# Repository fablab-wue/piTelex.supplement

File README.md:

# - piTelex.supplement

This project hold the additional files for the teletype project [piTelex](https://github.com/fablab-wue/piTelex)

**[For more informations see the WIKI pages](https://github.com/fablab-wue/piTelex/wiki)**

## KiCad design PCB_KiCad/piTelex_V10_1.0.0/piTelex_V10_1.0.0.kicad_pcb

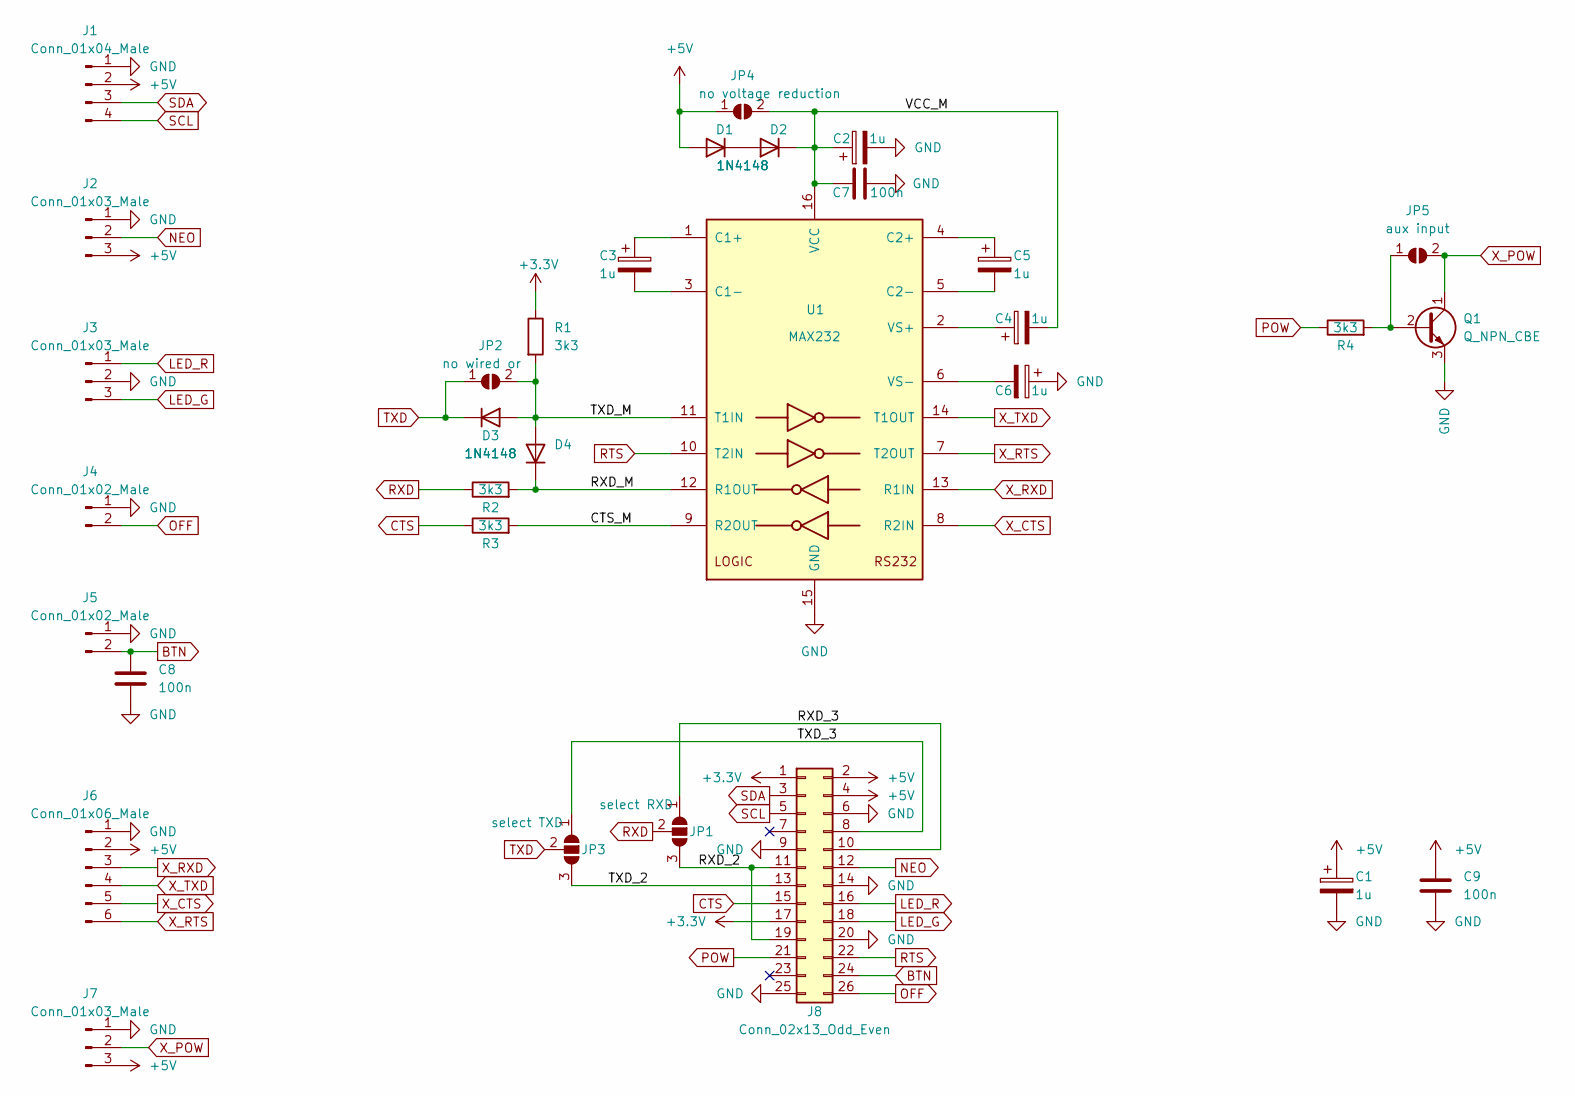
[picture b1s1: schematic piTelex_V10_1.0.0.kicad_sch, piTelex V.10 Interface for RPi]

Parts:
C1, C2, C3, C4, C5, C6: 1u; CP_Radial_D4.0mm_P2.00mm
C7, C8, C9: 100n; C_Disc_D3.4mm_W2.1mm_P2.50mm
D1, D2, D3, D4: 1N4148; D_DO-35_SOD27_P7.62mm_Horizontal
J1: Conn_01x04_Male; PinHeader_1x04_P2.54mm_Vertical
J2, J3, J7: Conn_01x03_Male; PinHeader_1x03_P2.54mm_Vertical
J4, J5: Conn_01x02_Male; PinHeader_1x02_P2.54mm_Vertical
J6: Conn_01x06_Male; PinHeader_1x06_P2.54mm_Vertical
J8: Conn_02x13_Odd_Even; PinSocket_2x13_P2.54mm_Vertical
JP1: select RXD; SolderJumper-3_P1.3mm_Open_Pad1.0x1.5mm
JP2: no wired or; SolderJumper-2_P1.3mm_Open_Pad1.0x1.5mm
JP3: select TXD; SolderJumper-3_P1.3mm_Open_Pad1.0x1.5mm
JP4: no voltage reduction; SolderJumper-2_P1.3mm_Open_Pad1.0x1.5mm
JP5: aux input; SolderJumper-2_P1.3mm_Open_Pad1.0x1.5mm
Q1: Q_NPN_CBE; TO-92L
R1, R2, R3, R4: 3k3; R_Axial_DIN0207_L6.3mm_D2.5mm_P10.16mm_Horizontal
U1: MAX232; DIP-16_W7.62mm

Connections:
+3.3V: J8.1, J8.17, R1.1
+5V: C1.1, C9.1, D1.2 (A), J1.2, J2.3, J6.2, J7.3, J8.2, J8.4, JP4.1 (A)
/CTS_M: R3.2, U1.9 (R2OUT)
/RXD_2: J8.11, J8.19, JP1.3 (B)
/RXD_3: J8.10, JP1.1 (A)
/RXD_M: D4.1 (K), R2.2, U1.12 (R1OUT)
/TXD_2: J8.13, JP3.3 (B)
/TXD_3: J8.8, JP3.1 (A)
/TXD_M: D3.2 (A), D4.2 (A), JP2.2 (B), R1.2, U1.11 (T1IN)
/VCC_M: C2.1, C4.2, C7.1, D2.1 (K), JP4.2 (B), U1.16 (VCC)
BTN: C8.1, J5.2, J8.24
CTS: J8.15, R3.1
GND: C1.2, C2.2, C6.1, C7.2, C8.2, C9.2, J1.1, J2.1, J3.2, J4.1, J5.1, J6.1, J7.1, J8.6, J8.9, J8.14, J8.20, J8.25, Q1.3 (E), U1.15 (GND)
LED_G: J3.3, J8.18
LED_R: J3.1, J8.16
NEO: J2.2, J8.12
unnamed: C3.1, U1.1 (C1+)
unnamed: C3.2, U1.3 (C1-)
unnamed: C4.1, U1.2 (VS+)
unnamed: C5.1, U1.4 (C2+)
unnamed: C5.2, U1.5 (C2-)
unnamed: C6.2, U1.6 (VS-)
unnamed: D1.1 (K), D2.2 (A)
unnamed: JP5.1 (A), Q1.2 (B), R4.2
OFF: J4.2, J8.26
POW: J8.21, R4.1
RTS: J8.22, U1.10 (T2IN)
RXD: JP1.2 (C), R2.1
SCL: J1.4, J8.5
SDA: J1.3, J8.3
TXD: D3.1 (K), JP2.1 (A), JP3.2 (C)
X_CTS: J6.5, U1.8 (R2IN)
X_POW: J7.2, JP5.2 (B), Q1.1 (C)
X_RTS: J6.6, U1.7 (T2OUT)
X_RXD: J6.3, U1.13 (R1IN)
X_TXD: J6.4, U1.14 (T1OUT)

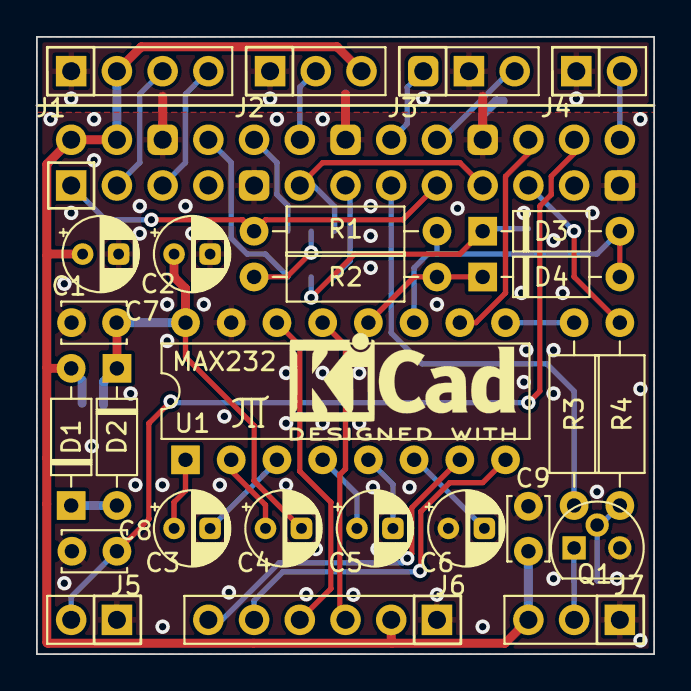
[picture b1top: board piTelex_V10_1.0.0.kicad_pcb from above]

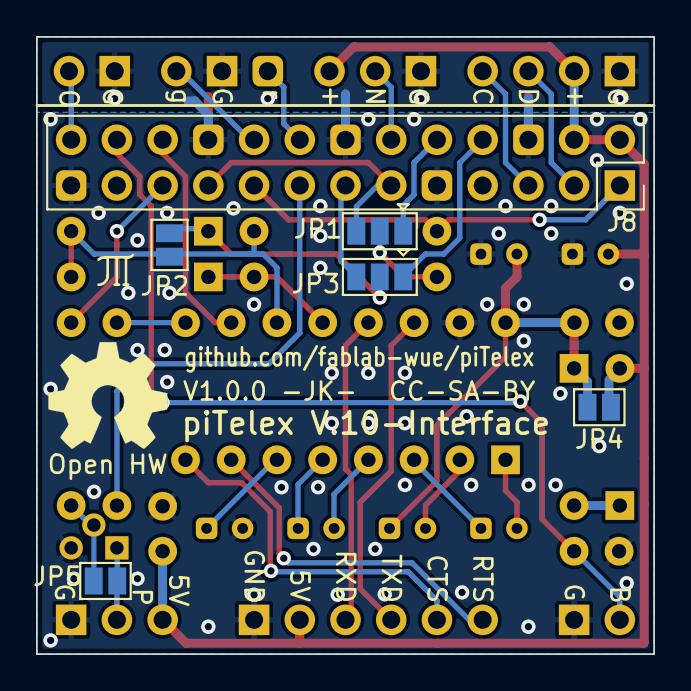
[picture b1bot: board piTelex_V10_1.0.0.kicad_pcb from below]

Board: 2 copper layers, 34.3 x 34.3 mm, 32 parts (6 on the bottom side), 36 nets.

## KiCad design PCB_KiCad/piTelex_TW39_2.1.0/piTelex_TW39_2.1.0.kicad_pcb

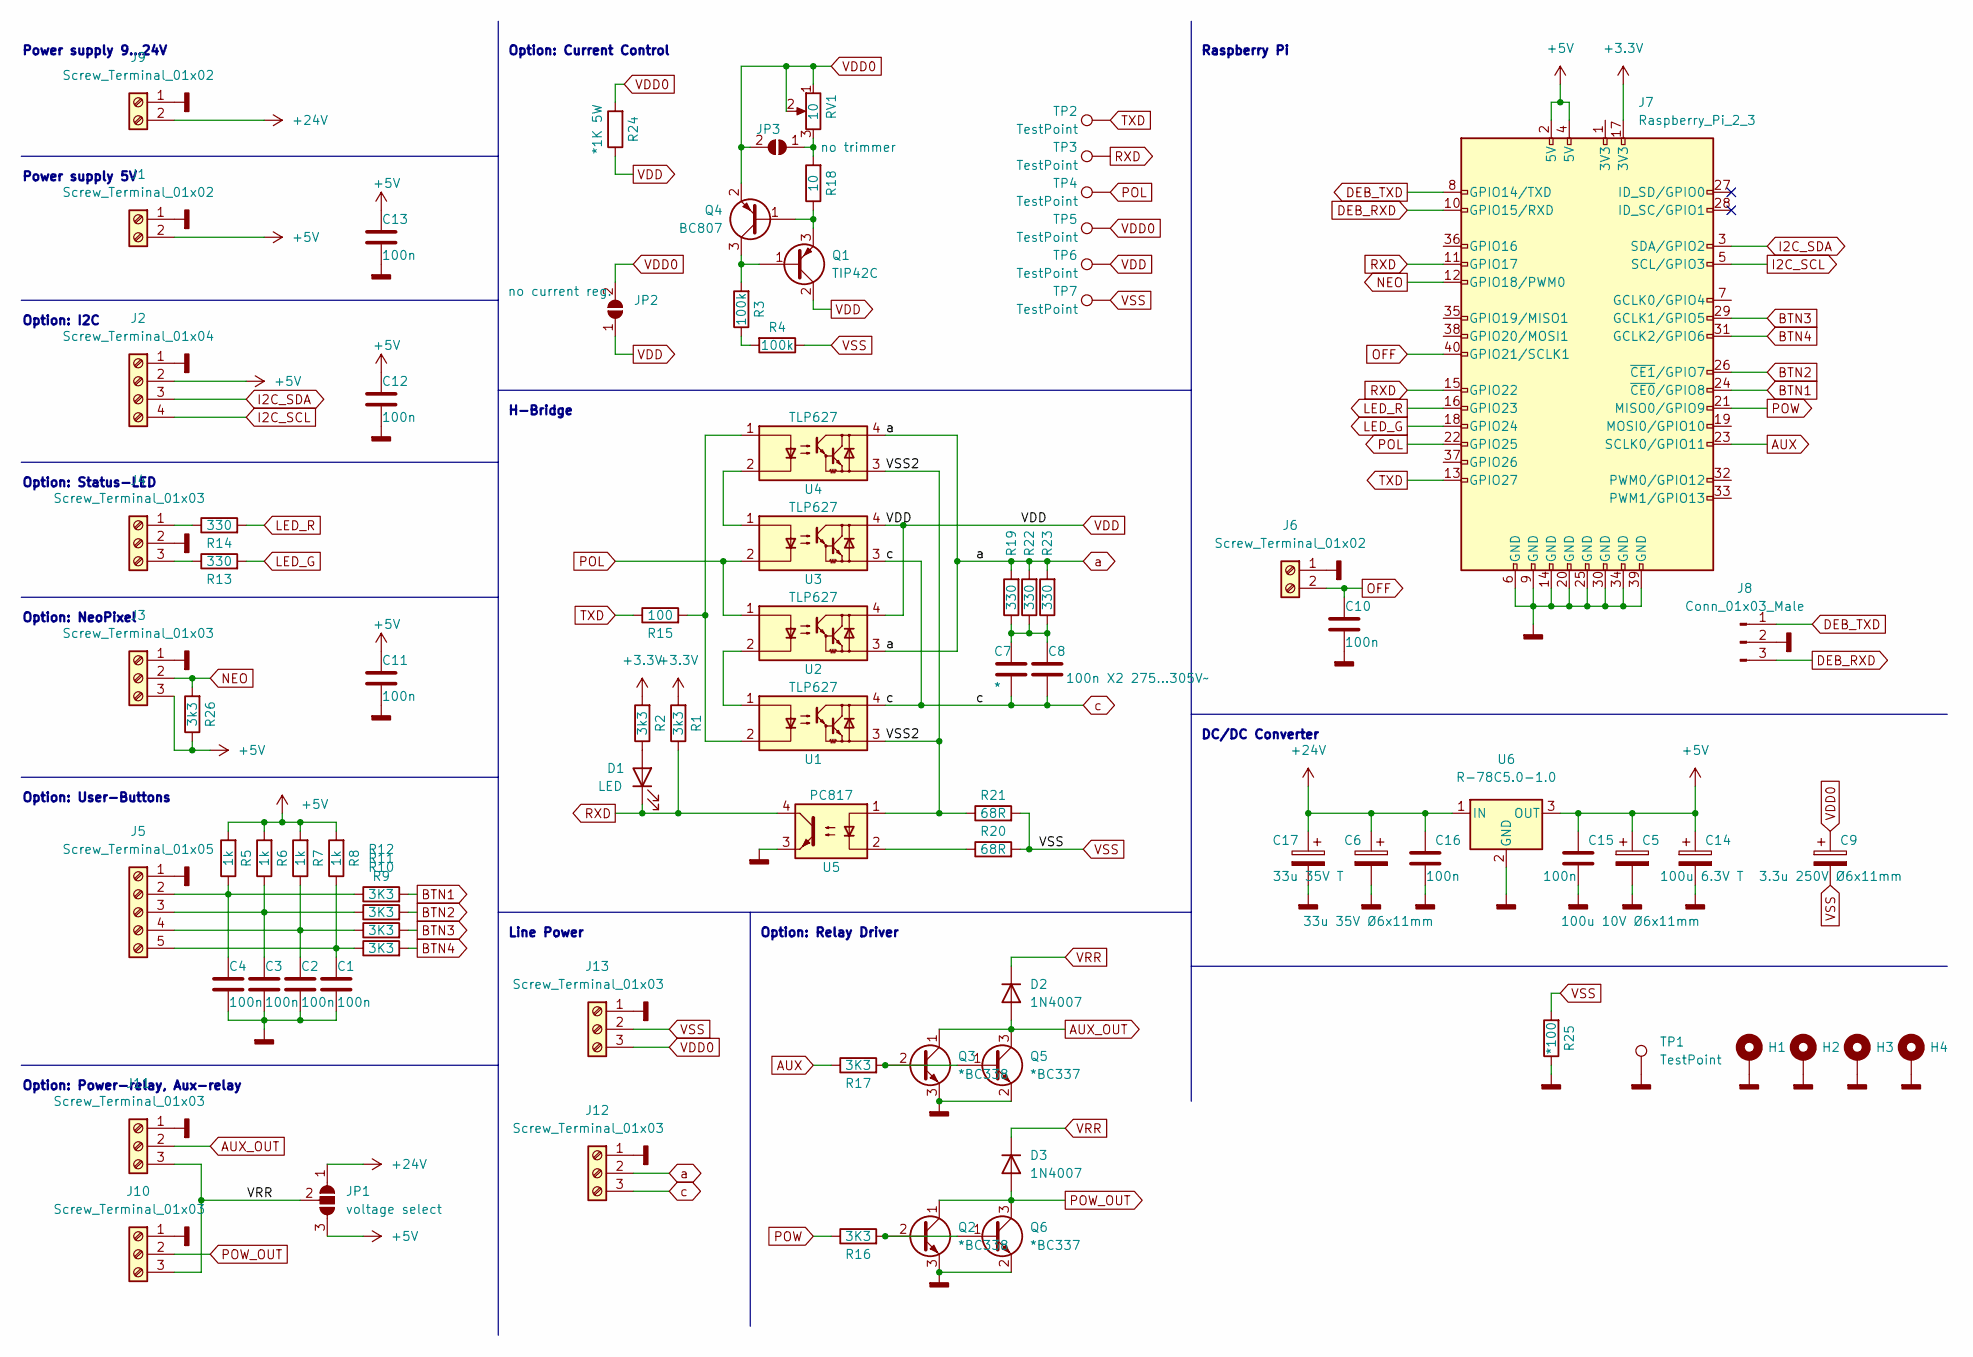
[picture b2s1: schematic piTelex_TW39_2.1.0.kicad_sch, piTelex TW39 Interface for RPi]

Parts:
C1, C2, C3, C4, C10, C11, C12, C13, C15, C16: 100n; C_0805_2012Metric_Pad1.18x1.45mm_HandSolder
C5: 100u 10V Ø6x11mm; CP_Radial_D7.5mm_P2.50mm
C6: 33u 35V Ø6x11mm; CP_Radial_D7.5mm_P2.50mm
C7: *; C_Rect_L9.0mm_W4.2mm_P7.50mm_MKT
C8: 100n X2 275...305V~; C_Rect_L16.5mm_W6.0mm_P15.00mm_MKT
C9: 3.3u 250V Ø6x11mm; CP_Radial_D7.5mm_P2.50mm
C14: 100u 6.3V T; CP_EIA-7343-31_Kemet-D_Pad2.25x2.55mm_HandSolder
C17: 33u 35V T; CP_EIA-7343-31_Kemet-D_Pad2.25x2.55mm_HandSolder
D1: LED; LED_D5.0mm
D2, D3: 1N4007; D_SMB
H1, H2, H3, H4: MountingHole_Pad; MountingHole_2.7mm_M2.5_ISO7380_Pad
J1, J6, J9: Screw_Terminal_01x02; Molex_KK-254_AE-6410-02A_1x02_P2.54mm_Vertical
J2: Screw_Terminal_01x04; Molex_KK-254_AE-6410-04A_1x04_P2.54mm_Vertical
J3, J4, J10, J11, J12, J13: Screw_Terminal_01x03; Molex_KK-254_AE-6410-03A_1x03_P2.54mm_Vertical
J5: Screw_Terminal_01x05; Molex_KK-254_AE-6410-05A_1x05_P2.54mm_Vertical
J7: Raspberry_Pi_2_3; PinSocket_2x20_P2.54mm_Vertical
J8: Conn_01x03_Male; PinHeader_1x03_P2.54mm_Vertical
JP1: voltage select; SolderJumper-3_P1.3mm_Open_Pad1.0x1.5mm
JP2: no current reg.; SolderJumper-2_P1.3mm_Open_Pad1.0x1.5mm
JP3: no trimmer; SolderJumper-2_P1.3mm_Open_Pad1.0x1.5mm
Q1: TIP42C; TO-220-3_Vertical
Q2, Q3: *BC338; TO-92
Q4: BC807; SOT-23
Q5, Q6: *BC337; SOT-23
R1, R2, R26: 3k3; R_0805_2012Metric_Pad1.20x1.40mm_HandSolder
R3, R4: 100k; R_0805_2012Metric_Pad1.20x1.40mm_HandSolder
R5, R6, R7, R8: 1k; R_0805_2012Metric_Pad1.20x1.40mm_HandSolder
R9, R10, R11, R12, R16, R17: 3K3; R_0805_2012Metric_Pad1.20x1.40mm_HandSolder
R13, R14, R19, R22, R23: 330; R_0805_2012Metric_Pad1.20x1.40mm_HandSolder
R15: 100; R_0805_2012Metric_Pad1.20x1.40mm_HandSolder
R18: 10; R_0805_2012Metric_Pad1.20x1.40mm_HandSolder
R20, R21: 68R; R_0805_2012Metric_Pad1.20x1.40mm_HandSolder
R24: *1K 5W; R_Axial_Power_L25.0mm_W9.0mm_P30.48mm
R25: *100; R_0805_2012Metric_Pad1.20x1.40mm_HandSolder
RV1: 10; Potentiometer_Bourns_3299Z_Horizontal
TP1: TestPoint; Pin_D1.0mm_L10.0mm
TP2, TP3, TP4, TP5, TP6, TP7: TestPoint; TestPoint_Pad_D1.5mm
U1, U2, U3, U4: TLP627; DIP-4_W7.62mm
U5: PC817; DIP-4_W7.62mm
U6: R-78C5.0-1.0; Converter_DCDC_RECOM_R-78E-0.5_THT

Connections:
+3.3V: J7.17 (3V3), R1.2, R2.2
+5V: C5.1, C11.1, C12.1, C13.1, C14.1, C15.1, J1.2, J2.2, J3.3, J7.2 (5V), J7.4 (5V), JP1.3 (B), R5.2, R6.2, R7.2, R8.2, R26.1, U6.3 (OUT)
+24V: C6.1, C16.1, C17.1, J9.2, JP1.1 (A), U6.1 (IN)
/VSS2: R21.1, U1.3, U4.3, U5.1
AUX: J7.23 (SCLK0/GPIO11), R17.1
AUX_OUT: D2.2 (A), J11.2, Q3.1 (C), Q5.3 (C)
BTN1: J7.24 (~CE0/GPIO8), R12.2
BTN2: J7.26 (~CE1/GPIO7), R11.2
BTN3: J7.29 (GCLK1/GPIO5), R10.2
BTN4: J7.31 (GCLK2/GPIO6), R9.2
DEB_RXD: J7.10 (GPIO15/RXD), J8.3
DEB_TXD: J7.8 (GPIO14/TXD), J8.1
GNDD: C1.2, C2.2, C3.2, C4.2, C5.2, C6.2, C10.2, C11.2, C12.2, C13.2, C14.2, C15.2, C16.2, C17.2, H1.1, H2.1, H3.1, H4.1, J1.1, J2.1, J3.1, J4.2, J5.1, J6.1, J7.6 (GND), J7.9 (GND), J7.14 (GND), J7.20 (GND), J7.25 (GND), J7.30 (GND), J7.34 (GND), J7.39 (GND), J8.2, J9.1, J10.1, J11.1, J12.1, J13.1, Q2.3 (E), Q3.3 (E), Q5.2 (E), Q6.2 (E), R25.1, TP1.1, U5.3, U6.2 (GND)
I2C_SCL: J2.4, J7.5 (SCL/GPIO3)
I2C_SDA: J2.3, J7.3 (SDA/GPIO2)
LED_G: J7.18 (GPIO24), R13.2
LED_R: J7.16 (GPIO23), R14.2
NEO: J3.2, J7.12 (GPIO18/PWM0), R26.2
unnamed: C1.1, J5.5, R8.1, R9.1
unnamed: C2.1, J5.4, R7.1, R10.1
unnamed: C3.1, J5.3, R6.1, R11.1
unnamed: C4.1, J5.2, R5.1, R12.1
unnamed: C7.1, C8.1, R19.1, R22.1, R23.1
unnamed: J4.1, R14.1
unnamed: J4.3, R13.1
unnamed: Q3.2 (B), Q5.1 (B), R17.2
unnamed: Q1.3 (E), Q4.1 (B), R18.1
unnamed: Q1.1 (B), Q4.3 (C), R3.2
unnamed: Q2.2 (B), Q6.1 (B), R16.2
unnamed: D1.2 (A), R2.1
unnamed: R3.1, R4.2
unnamed: JP3.1 (A), R18.2, RV1.3
unnamed: U1.1, U2.2
unnamed: R15.2, U1.2, U4.1
unnamed: U3.1, U4.2
unnamed: R20.1, U5.2
OFF: C10.1, J6.2, J7.40 (GPIO21/SCLK1)
POL: J7.22 (GPIO25), TP4.1, U2.1, U3.2
POW: J7.21 (MISO0/GPIO9), R16.1
POW_OUT: D3.2 (A), J10.2, Q2.1 (C), Q6.3 (C)
RXD: D1.1 (K), J7.11 (GPIO17), J7.15 (GPIO22), R1.1, TP3.1, U5.4
TXD: J7.13 (GPIO27), R15.1, TP2.1
VDD: JP2.1 (A), Q1.2 (C), R24.1, TP6.1, U2.4, U3.4
VDD0: C9.1, J13.3, JP2.2 (B), JP3.2 (B), Q4.2 (E), R24.2, RV1.1, RV1.2, TP5.1
VRR: D2.1 (K), D3.1 (K), J10.3, J11.3, JP1.2 (C)
VSS: C9.2, J13.2, R4.1, R20.2, R21.2, R25.2, TP7.1
a: J12.2, R19.2, R22.2, R23.2, U2.3, U4.4
c: C7.2, C8.2, J12.3, U1.4, U3.3

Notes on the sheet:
Line Power
Option: Relay Driver
Option: Status-LED
Option: User-Buttons
Option: I2C
Raspberry Pi
Power supply 9...24V
Option: Current Control
Option: NeoPixel
Power supply 5V
DC/DC Converter
Option: Power-relay, Aux-relay
H-Bridge

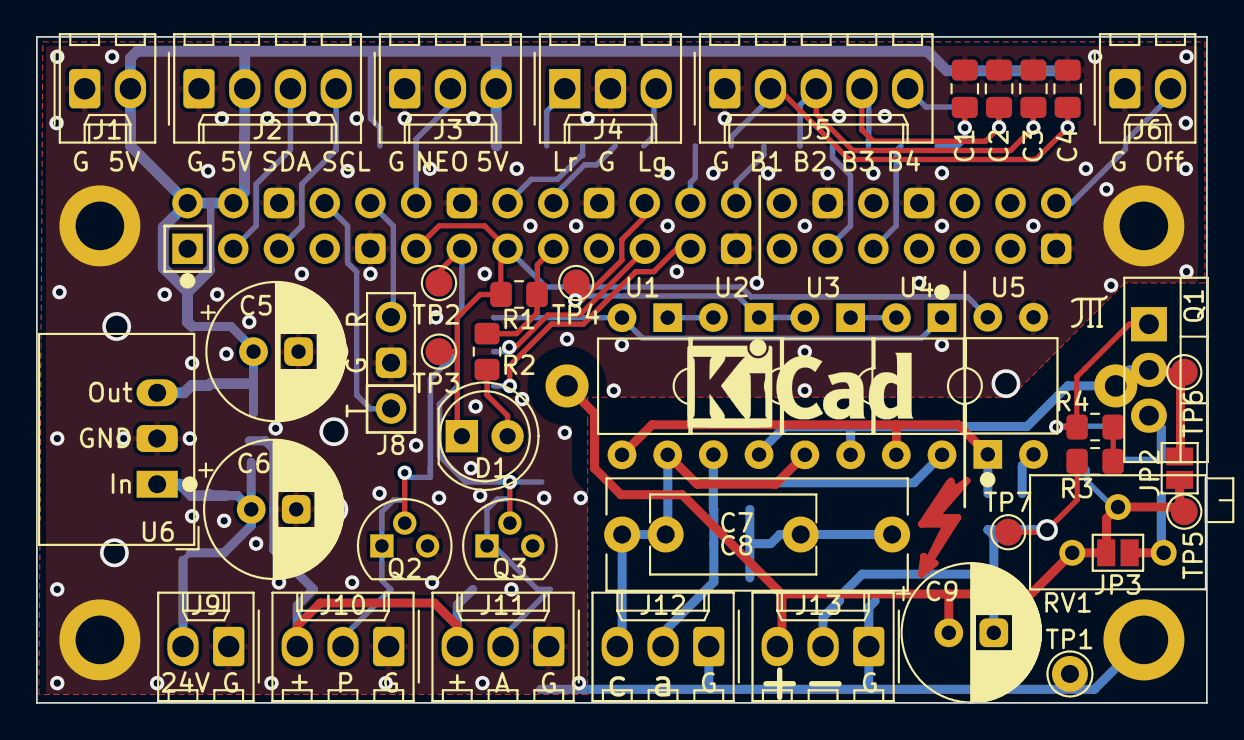
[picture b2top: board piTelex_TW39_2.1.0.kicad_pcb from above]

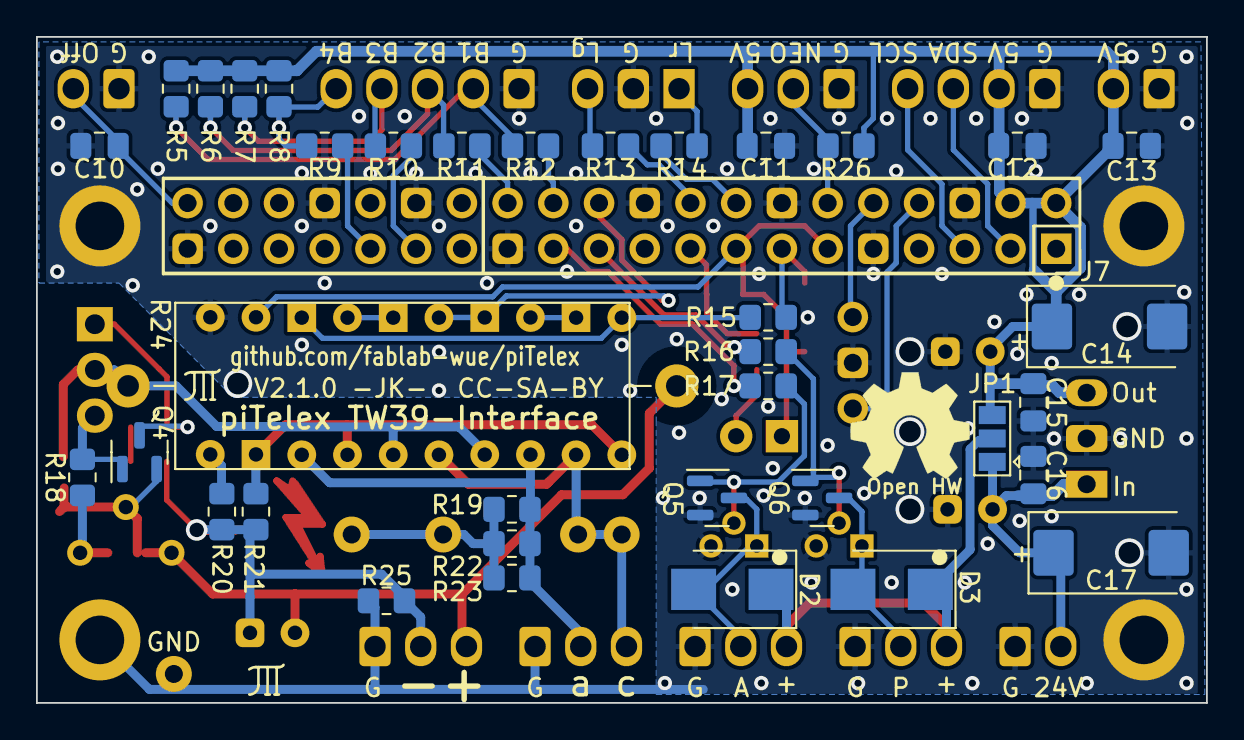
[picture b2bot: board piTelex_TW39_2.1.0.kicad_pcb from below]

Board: 2 copper layers, 65.0 x 37.0 mm, 88 parts (37 on the bottom side), 48 nets.

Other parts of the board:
KiCAD Logo: KiCad-Logo_5mm_SilkScreen
KiCAD Logo#2: Symbol_Highvoltage_Type1_CopperTop_Small

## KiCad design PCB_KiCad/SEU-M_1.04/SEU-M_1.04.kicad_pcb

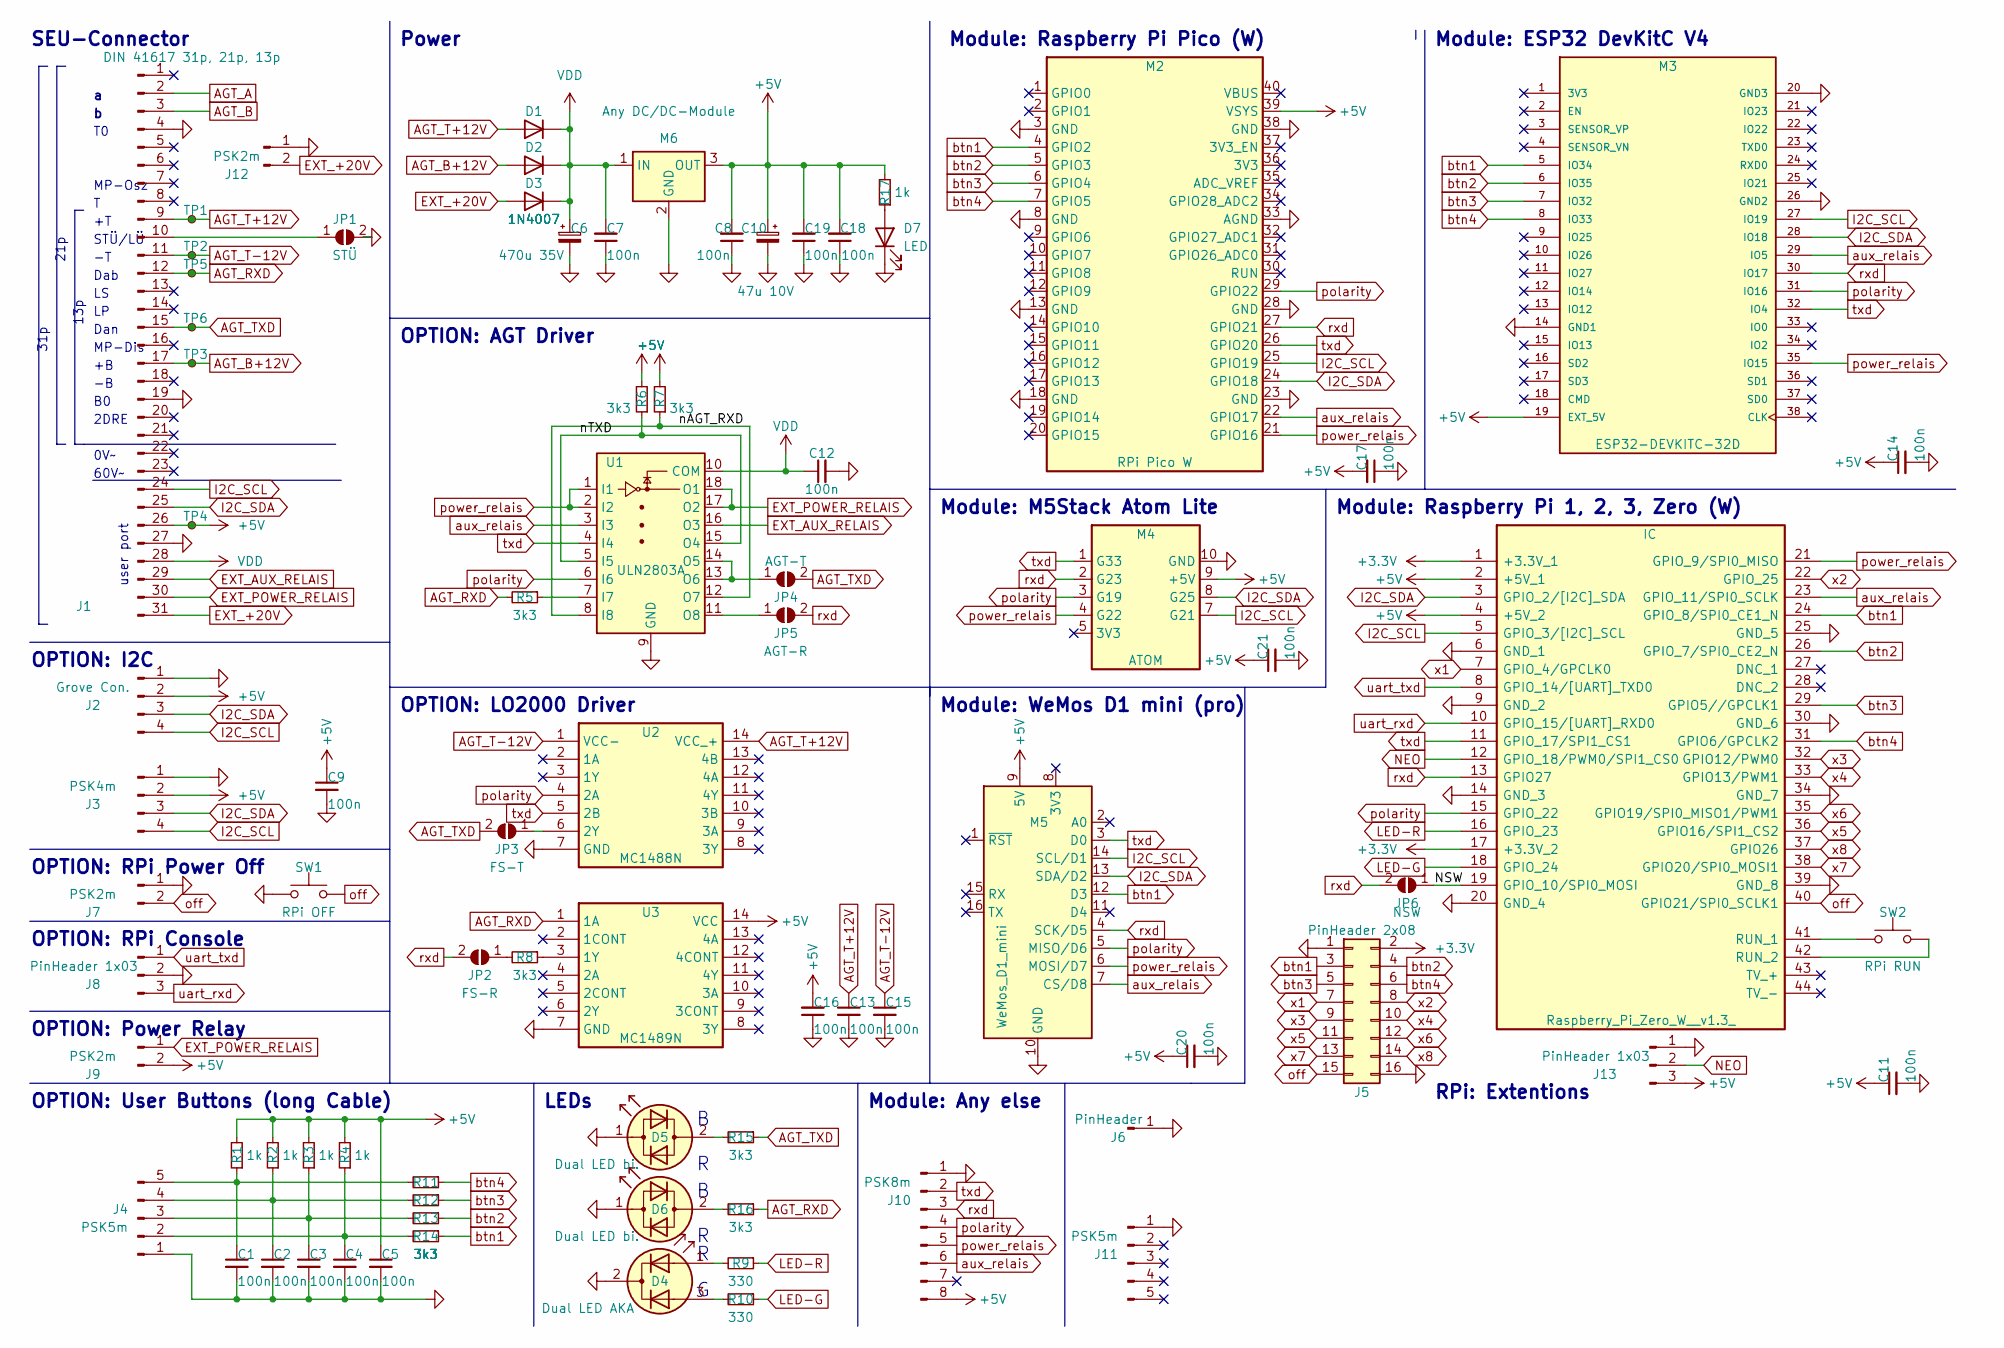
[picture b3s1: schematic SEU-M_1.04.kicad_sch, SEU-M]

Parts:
C1, C2, C3, C4, C5, C7, C8, C9, C11, C12, C13, C14, C15, C16, C17, C18, C19, C20, C21: 100n; C_Disc_D4.3mm_W1.9mm_P5.00mm
C6: 470u 35V; CP_Radial_D10.0mm_P2.50mm_P5.00mm
C10: 47u 10V; CP_Radial_D6.3mm_P2.50mm
D1, D2, D3: 1N4007; D_DO-41_SOD81_P10.16mm_Horizontal
D4: Dual LED AKA; LED_D3.0mm-3
D5, D6: Dual LED bi.; LED_D3.0mm
D7: LED; LED_D5.0mm
IC: Raspberry_Pi_Zero_W__v1.3_; RASPBERRYPIZEROWV13; Manufacturer_Part_Number Raspberry Pi Zero W (v1.3)
J1: DIN 41617 31p, 21p, 13p; DIN41617
J2: Grove Con.; JST_PH_B4B-PH-K_1x04_P2.00mm_Vertical
J3: PSK4m; Molex_KK-254_AE-6410-04A_1x04_P2.54mm_Vertical
J4, J11: PSK5m; Molex_KK-254_AE-6410-05A_1x05_P2.54mm_Vertical
J5: PinHeader 2x08; PinHeader_2x08_P2.54mm_Vertical
J6: PinHeader; PinHeader_1x01_P2.54mm_Vertical
J7, J9, J12: PSK2m; Molex_KK-254_AE-6410-02A_1x02_P2.54mm_Vertical
J8, J13: PinHeader 1x03; PinHeader_1x03_P2.54mm_Vertical
J10: PSK8m; Molex_KK-254_AE-6410-08A_1x08_P2.54mm_Vertical
JP1: STÜ; SolderJumper-2_P1.3mm_Open_RoundedPad1.0x1.5mm
JP2: FS-R; SolderJumper-2_P1.3mm_Open_RoundedPad1.0x1.5mm
JP3: FS-T; SolderJumper-2_P1.3mm_Open_RoundedPad1.0x1.5mm
JP4: AGT-T; SolderJumper-2_P1.3mm_Open_RoundedPad1.0x1.5mm
JP5: AGT-R; SolderJumper-2_P1.3mm_Open_RoundedPad1.0x1.5mm
JP6: NSW; SolderJumper-2_P1.3mm_Open_RoundedPad1.0x1.5mm
M2: RPi Pico W; RPi_Pico
M3: ESP32-DEVKITC-32D; MODULE_ESP32-DEVKITC-32D; PARTREV 4
M4: ATOM
M5: WeMos_D1_mini; WEMOS_D1_mini_light
M6: Any DC/DC-Module; DC_DC
R1, R2, R3, R4, R17: 1k; R_Axial_DIN0207_L6.3mm_D2.5mm_P10.16mm_Horizontal
R5, R6, R7, R8, R11, R12, R13, R14, R15, R16: 3k3; R_Axial_DIN0207_L6.3mm_D2.5mm_P10.16mm_Horizontal
R9, R10: 330; R_Axial_DIN0207_L6.3mm_D2.5mm_P10.16mm_Horizontal
SW1: RPi OFF; SW_PUSH_6mm
SW2: RPi RUN; SW_PUSH_6mm
TP1, TP2, TP3, TP4, TP5, TP6: TestPoint_Small; TestPoint_Pad_D1.5mm
U1: ULN2803A; DIP-18_W7.62mm
U2: MC1488N; DIP-14_W7.62mm
U3: MC1489N; DIP-14_W7.62mm

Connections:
+3.3V: IC.1 (+3.3V_1), IC.17 (+3.3V_2), J5.2
+5V: C5.1, C8.2, C9.1, C10.1, C11.1, C14.1, C16.2, C17.2, C18.2, C19.2, C20.1, C21.1, IC.2 (+5V_1), IC.4 (+5V_2), J1.26, J2.2, J3.2, J9.2, J10.8, J13.3, M2.39 (VSYS), M3.19 (EXT_5V), M4.9 (+5V), M5.9 (5V), M6.3 (OUT), R1.2, R2.2, R3.2, R4.2, R6.2, R7.2, R17.2, TP4.1, U3.14 (VCC)
/NSW: IC.19 (GPIO_10/SPI0_MOSI), JP6.1 (A)
/nAGT_RXD: R7.1, U1.8 (I8), U1.12 (O7)
/nTXD: R6.1, U1.5 (I5), U1.15 (O4)
AGT_A: J1.2
AGT_B: J1.3
AGT_B+12V: D2.2 (A), J1.17, TP3.1
AGT_RXD: J1.12, R5.2, R16.1, TP5.1, U3.1 (1A)
AGT_T+12V: C13.1, D1.2 (A), J1.9, TP1.1, U2.14 (VCC_+)
AGT_T-12V: C15.1, J1.11, TP2.1, U2.1 (VCC-)
AGT_TXD: J1.15, JP3.2 (B), JP4.2 (B), R15.1, TP6.1
EXT_+20V: D3.2 (A), J1.31, J12.2
EXT_AUX_RELAIS: J1.29, U1.16 (O3)
EXT_POWER_RELAIS: J1.30, J9.1, U1.17 (O2), U1.18 (O1)
GND: C1.2, C2.2, C3.2, C4.2, C5.2, C6.2, C7.1, C8.1, C9.2, C10.2, C11.2, C12.2, C13.2, C14.2, C15.2, C16.1, C17.1, C18.1, C19.1, C20.2, C21.2, D4.2 (K), D5.1 (KA), D6.1 (KA), D7.1 (K), IC.6 (GND_1), IC.9 (GND_2), IC.14 (GND_3), IC.20 (GND_4), IC.25 (GND_5), IC.30 (GND_6), IC.34 (GND_7), IC.39 (GND_8), J1.4, J1.19, J1.27, J2.1, J3.1, J4.1, J5.1, J5.16, J6.1, J7.1, J8.2, J10.1, J11.1, J12.1, J13.1, JP1.2 (B), M2.3 (GND), M2.8 (GND), M2.13 (GND), M2.18 (GND), M2.23 (GND), M2.28 (GND), M2.33 (AGND), M2.38 (GND), M3.14 (GND1), M3.20 (GND3), M3.26 (GND2), M4.10 (GND), M5.10 (GND), M6.2 (GND), SW1.1, U1.9 (GND), U2.7 (GND), U3.7 (GND)
I2C_SCL: IC.5 (GPIO_3/[I2C]_SCL), J1.24, J2.4, J3.4, M2.25 (GPIO19), M3.27 (IO19), M4.7 (G21), M5.14 (SCL/D1)
I2C_SDA: IC.3 (GPIO_2/[I2C]_SDA), J1.25, J2.3, J3.3, M2.24 (GPIO18), M3.28 (IO18), M4.8 (G25), M5.13 (SDA/D2)
LED-G: IC.18 (GPIO_24), R10.1
LED-R: IC.16 (GPIO_23), R9.1
NEO: IC.12 (GPIO_18/PWM0/SPI1_CS0), J13.2
unnamed: C1.1, J4.5, R1.1, R11.2
unnamed: C2.1, J4.4, R2.1, R12.2
unnamed: C3.1, J4.3, R3.1, R13.2
unnamed: C4.1, J4.2, R4.1, R14.2
unnamed: D4.1 (A1), R9.2
unnamed: D4.3 (A2), R10.2
unnamed: D5.2 (AK), R15.2
unnamed: D6.2 (AK), R16.2
unnamed: D7.2 (A), R17.1
unnamed: J1.10, JP1.1 (A)
unnamed: JP2.1 (A), R8.2
unnamed: JP3.1 (A), U2.6 (2Y)
unnamed: JP4.1 (A), U1.13 (O6), U1.14 (O5)
unnamed: JP5.1 (A), U1.11 (O8)
unnamed: IC.41 (RUN_1), SW2.1
unnamed: IC.42 (RUN_2), SW2.2
unnamed: R5.1, U1.7 (I7)
unnamed: R8.1, U3.3 (1Y)
VDD: C6.1, C7.2, C12.1, D1.1 (K), D2.1 (K), D3.1 (K), J1.28, M6.1 (IN), U1.10 (COM)
aux_relais: IC.23 (GPIO_11/SPI0_SCLK), J10.6, M2.22 (GPIO17), M3.29 (IO5), M5.7 (CS/D8), U1.3 (I3)
btn1: IC.24 (GPIO_8/SPI0_CE1_N), J5.3, M2.4 (GPIO2), M3.5 (IO34), M5.12 (D3), R14.1
btn2: IC.26 (GPIO_7/SPI0_CE2_N), J5.4, M2.5 (GPIO3), M3.6 (IO35), R13.1
btn3: IC.29 (GPIO5//GPCLK1), J5.5, M2.6 (GPIO4), M3.7 (IO32), R12.1
btn4: IC.31 (GPIO6/GPCLK2), J5.6, M2.7 (GPIO5), M3.8 (IO33), R11.1
off: IC.40 (GPIO21/SPI0_SCLK1), J5.15, J7.2, SW1.2
polarity: IC.15 (GPIO_22), J10.4, M2.29 (GPIO22), M3.31 (IO16), M4.3 (G19), M5.5 (MISO/D6), U1.6 (I6), U2.4 (2A)
power_relais: IC.21 (GPIO_9/SPI0_MISO), J10.5, M2.21 (GPIO16), M3.35 (IO15), M4.4 (G22), M5.6 (MOSI/D7), U1.1 (I1), U1.2 (I2)
rxd: IC.13 (GPIO27), J10.3, JP2.2 (B), JP5.2 (B), JP6.2 (B), M2.27 (GPIO21), M3.30 (IO17), M4.2 (G23), M5.4 (SCK/D5)
txd: IC.11 (GPIO_17/SPI1_CS1), J10.2, M2.26 (GPIO20), M3.32 (IO4), M4.1 (G33), M5.3 (D0), U1.4 (I4), U2.5 (2B)
uart_rxd: IC.10 (GPIO_15/[UART]_RXD0), J8.3
uart_txd: IC.8 (GPIO_14/[UART]_TXD0), J8.1
x1: IC.7 (GPIO_4/GPCLK0), J5.7
x2: IC.22 (GPIO_25), J5.8
x3: IC.32 (GPIO12/PWM0), J5.9
x4: IC.33 (GPIO13/PWM1), J5.10
x5: IC.36 (GPIO16/SPI1_CS2), J5.11
x6: IC.35 (GPIO19/SPI0_MISO1/PWM1), J5.12
x7: IC.38 (GPIO20/SPI0_MOSI1), J5.13
x8: IC.37 (GPIO26), J5.14

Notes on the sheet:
13p
Dan
OPTION: Power Relay
31p
OPTION: LO2000 Driver
STÜ/LÜ
Module: M5Stack Atom Lite
Module: WeMos D1 mini (pro)
user port
Module: Any else
OPTION: I2C
0V~
SEU-Connector
60V~
Module: ESP32 DevKitC V4
Dab
LEDs
2DRE
OPTION: RPi Console
Power
OPTION: User Buttons (long Cable)
Module: Raspberry Pi Pico (W)
RPi: Extentions
MP-Dis
OPTION: AGT Driver
21p
Module: Raspberry Pi 1, 2, 3, Zero (W)
MP-Osz
OPTION: RPi Power Off

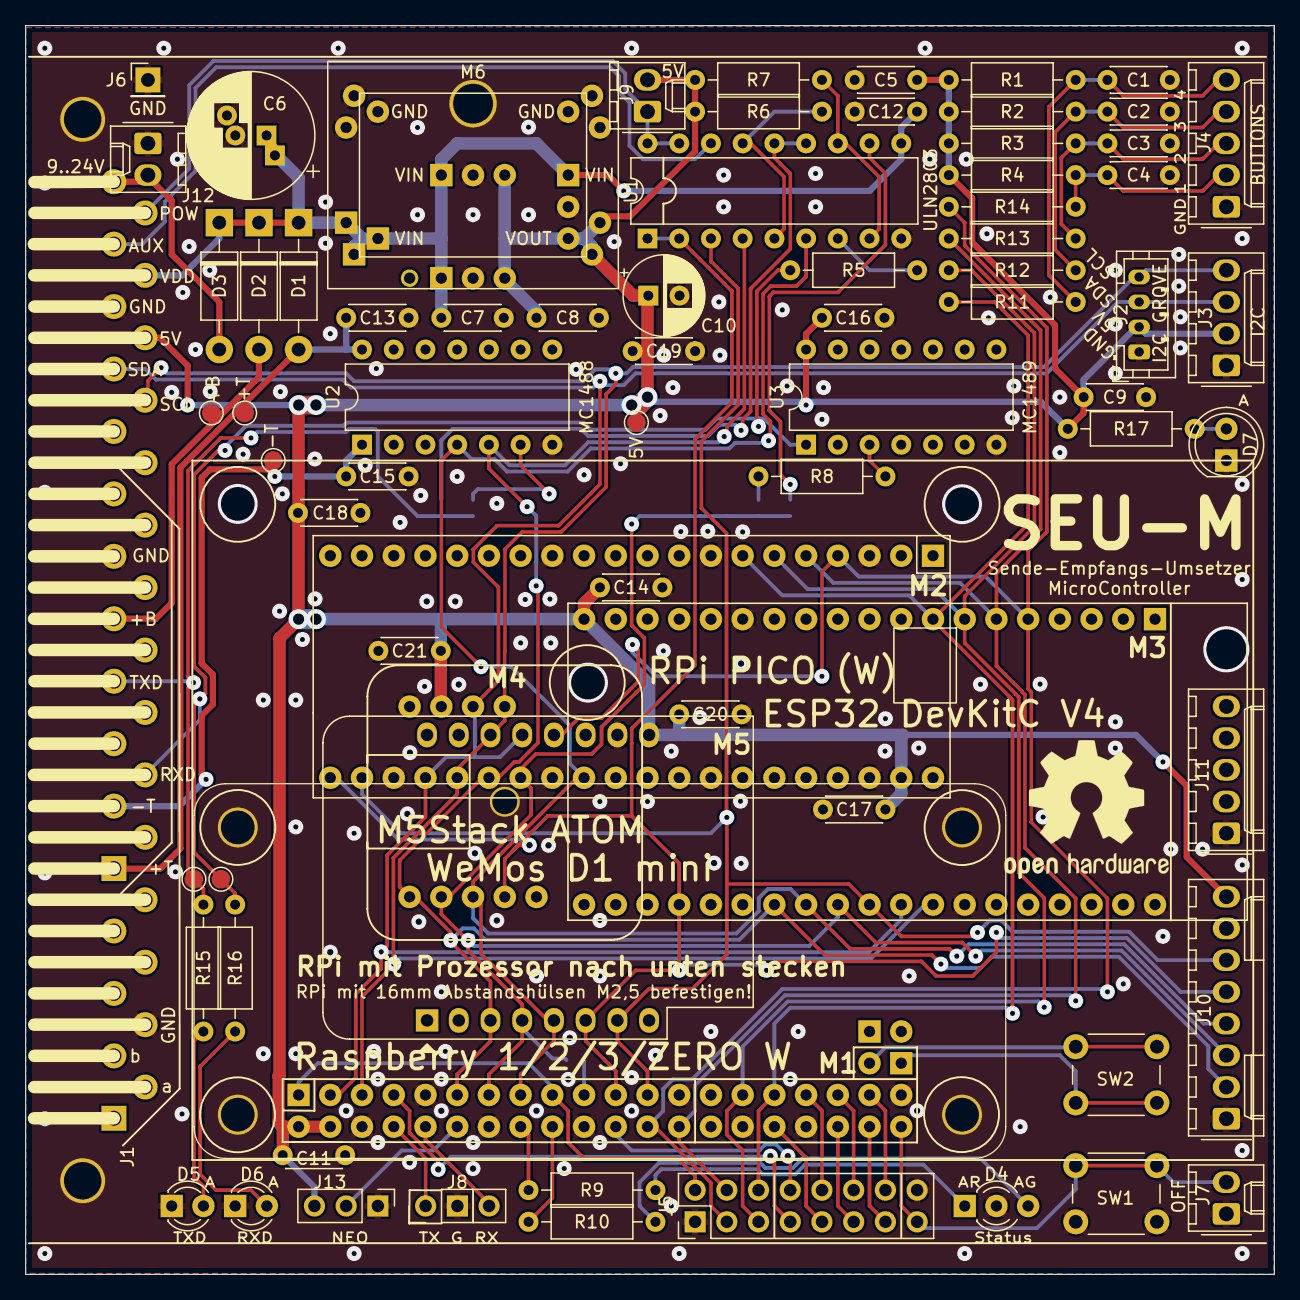
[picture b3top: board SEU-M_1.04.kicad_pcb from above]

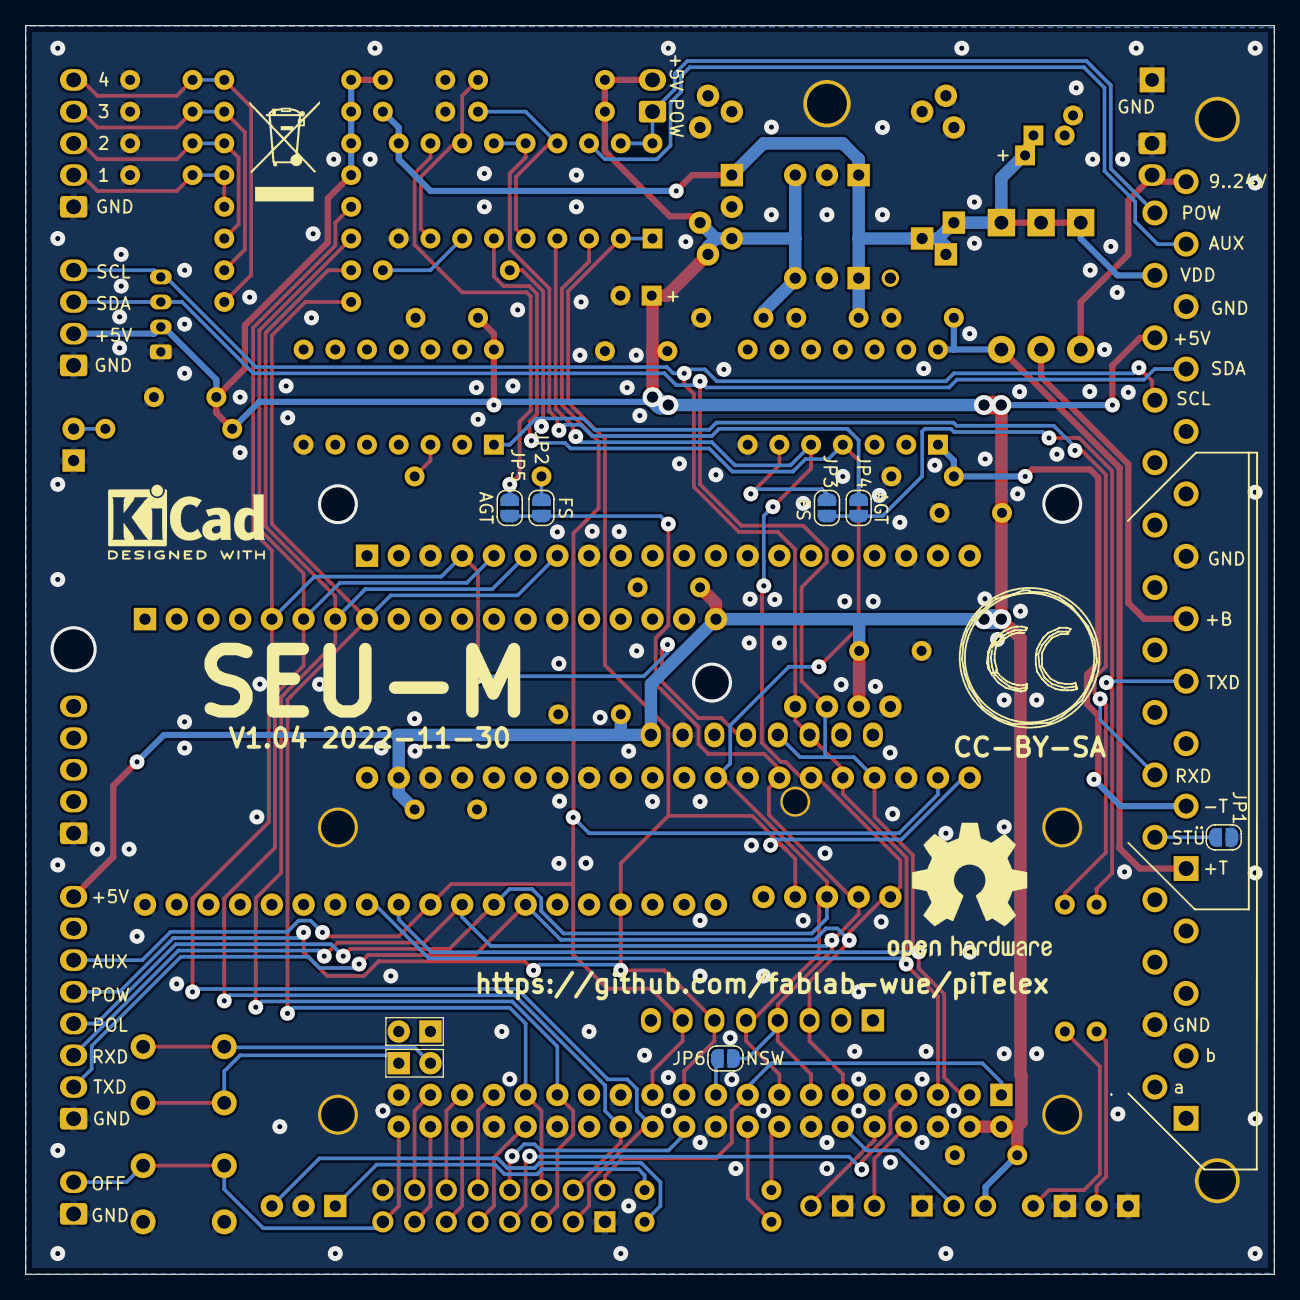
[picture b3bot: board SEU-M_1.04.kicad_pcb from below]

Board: 2 copper layers, 100.0 x 100.0 mm, 81 parts (7 on the bottom side), 58 nets.

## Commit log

2020-09-27 moved files from main project
2020-11-01 merged CoredDraw file from different locations
2022-12-06 Added PCB SEU-M_1.04
2023-02-16 added PCB piTelex_TW39_2.1.0
2023-02-16 added PCB piTelex_V10_1.0.0
2023-06-12 Delete pyTelex.pdf
    Part annotation doesn't match the eagle schematics file and the Layout png's
2023-06-12 Delete pyTelexSch.png
    Part annotation doesn't match the eagle schematics file and the Layout png's
2023-06-12 Add files via upload
    Schematics with correct parts annotation.

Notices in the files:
PCB_KiCad/SEU-M_1.04/SEU-M_1.04.kicad_pcb:
CC-BY-SA
